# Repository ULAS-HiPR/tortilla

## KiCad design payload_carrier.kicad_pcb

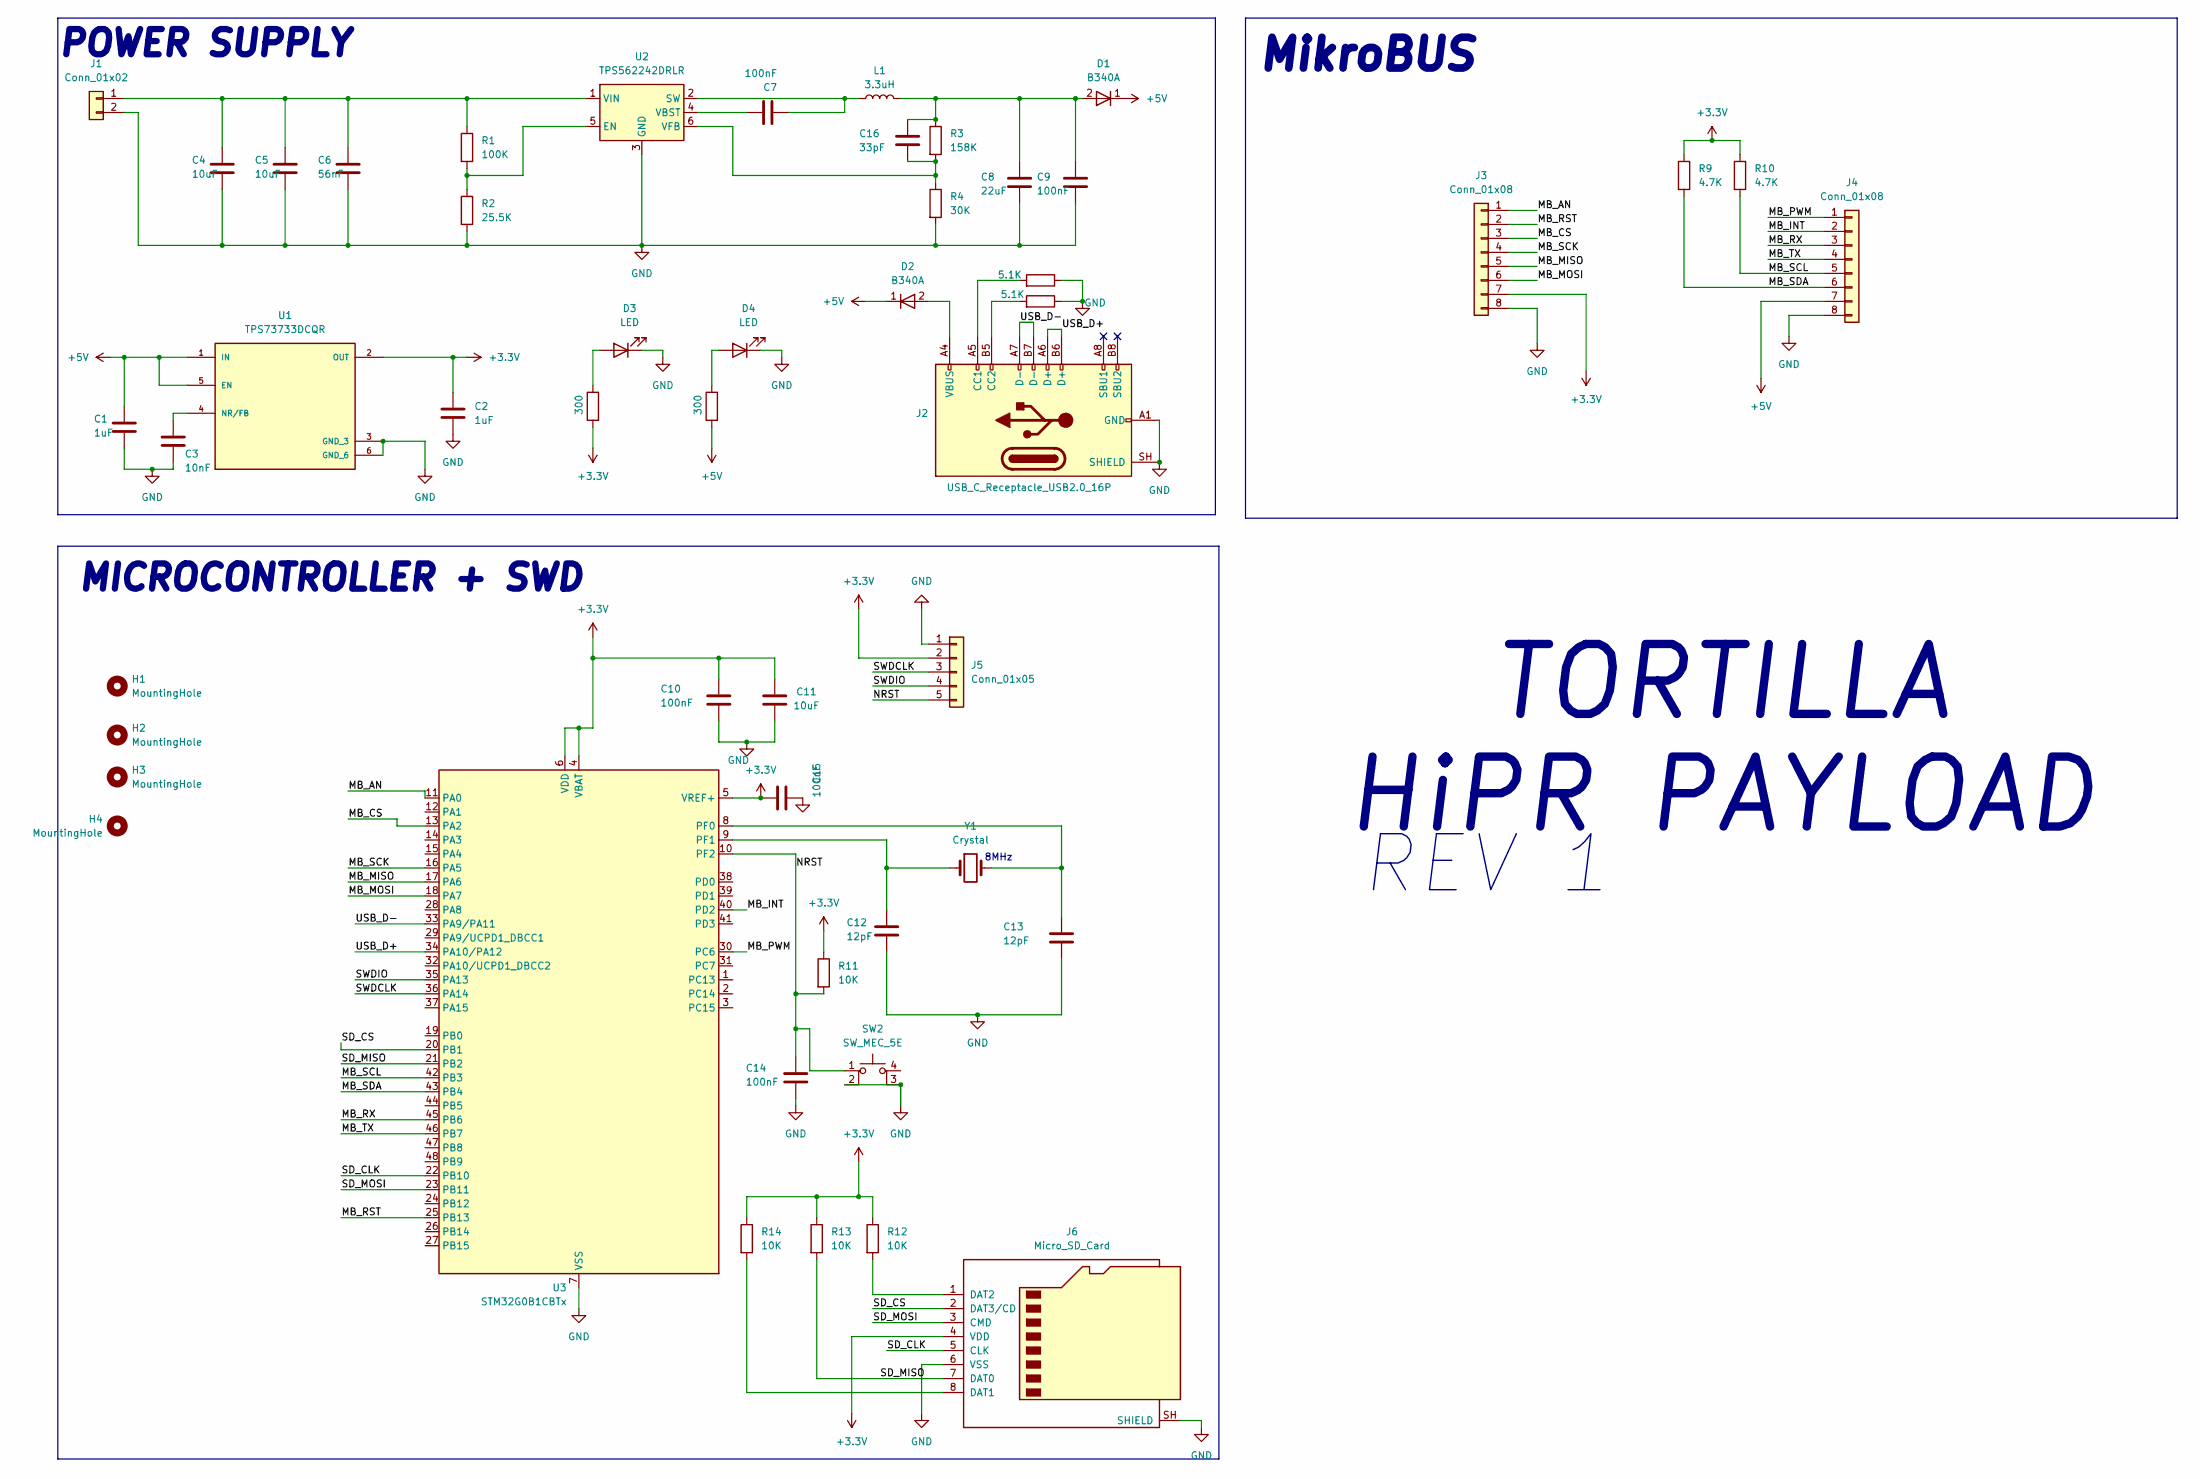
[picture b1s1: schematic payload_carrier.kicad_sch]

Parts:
C1, C2: 1uF; C_0603_1608Metric
C3: 10nF; C_0603_1608Metric
C4, C5, C11: 10uF; C_0805_2012Metric
C6: 56nF; C_0603_1608Metric
C7, C9, C10, C14, C15: 100nF; C_0603_1608Metric
C8: 22uF; C_0805_2012Metric
C12, C13: 12pF; C_0603_1608Metric
C16: 33pF; C_0603_1608Metric
D1, D2: B340A; D_SMA
D3, D4: LED; LED_0603_1608Metric
H1, H2, H3, H4: MountingHole; Mounting_Wuerth_WA-SMSI-M3_H0.5mm_9774005360
J1: Conn_01x02; JST_PH_B2B-PH-K_1x02_P2.00mm_Vertical
J2: USB_C_Receptacle_USB2.0_16P; USB_C_Receptacle_HRO_TYPE-C-31-M-12
J3, J4: Conn_01x08; PinSocket_1x08_P2.54mm_Vertical
J5: Conn_01x05; PinHeader_1x05_P2.54mm_Vertical
J6: Micro_SD_Card; microSD_HC_Wuerth_693072010801
L1: 3.3uH; L_Wuerth_MAPI-4020
R1: 100K; R_0603_1608Metric
R2: 25.5K; R_0603_1608Metric
R3: 158K; R_0603_1608Metric
R4: 30K; R_0603_1608Metric
R5, R6: 5.1K; R_0603_1608Metric
R7, R8: 300; R_0603_1608Metric
R9, R10: 4.7K; R_0603_1608Metric
R11, R12, R13, R14: 10K; R_0603_1608Metric
SW2: SW_MEC_5E; SW_SPST_B3SL-1002P
U1: TPS73733DCQR; IC_TPS73733DCQR; PARTREV R
U2: TPS562242DRLR; SOT-563
U3: STM32G0B1CBTx; LQFP-48_7x7mm_P0.5mm
Y1: Crystal; Crystal_SMD_5032-2Pin_5.0x3.2mm

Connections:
+3.3V: C2.1, C10.1, C11.1, C15.1, J3.7, J5.2, J6.4 (VDD), R7.2, R9.1, R10.1, R11.1, R12.1, R13.1, R14.1, U1.2 (OUT), U3.4 (VBAT), U3.5 (VREF+), U3.6 (VDD)
+5V: C1.1, D1.1 (K), D2.1 (K), J4.7, R8.2, U1.1 (IN), U1.5 (EN)
/MB_AN: J3.1, U3.11 (PA0)
/MB_CS: J3.3, U3.13 (PA2)
/MB_INT: J4.2, U3.40 (PD2)
/MB_MISO: J3.5, U3.17 (PA6)
/MB_MOSI: J3.6, U3.18 (PA7)
/MB_PWM: J4.1, U3.30 (PC6)
/MB_RST: J3.2, U3.25 (PB13)
/MB_RX: J4.3, U3.45 (PB6)
/MB_SCK: J3.4, U3.16 (PA5)
/MB_SCL: J4.5, R10.2, U3.42 (PB3)
/MB_SDA: J4.6, R9.2, U3.43 (PB4)
/MB_TX: J4.4, U3.46 (PB7)
/NRST: C14.1, J5.5, R11.2, SW2.1, U3.10 (PF2)
/SD_CLK: J6.5 (CLK), U3.22 (PB10)
/SD_CS: J6.2 (DAT3/CD), U3.20 (PB1)
/SD_MISO: J6.7 (DAT0), R13.2, U3.21 (PB2)
/SD_MOSI: J6.3 (CMD), U3.23 (PB11)
/SWDCLK: J5.3, U3.36 (PA14)
/SWDIO: J5.4, U3.35 (PA13)
/USB_D+: J2.A6 (D+), J2.B6 (D+), U3.34 (PA10/PA12)
/USB_D-: J2.A7 (D-), J2.B7 (D-), U3.33 (PA9/PA11)
GND: C1.2, C2.2, C3.2, C4.2, C5.2, C6.2, C8.2, C9.2, C10.2, C11.2, C12.2, C13.2, C14.2, C15.2, D3.1 (K), D4.1 (K), J1.2, J2.A1 (GND), J2.A12 (GND), J2.B1 (GND), J2.B12 (GND), J2.SH (SHIELD), J3.8, J4.8, J5.1, J6.6 (VSS), J6.SH (SHIELD), R2.2, R4.2, R5.1, R6.1, SW2.2, SW2.3 (K), U1.3 (GND_3), U1.6 (GND_6), U2.3 (GND), U3.7 (VSS)
unnamed: C8.1, C9.1, C16.1, D1.2 (A), L1.2, R3.1
unnamed: D2.2 (A), J2.A4 (VBUS), J2.A9 (VBUS), J2.B4 (VBUS), J2.B9 (VBUS)
unnamed: D3.2 (A), R7.1
unnamed: D4.2 (A), R8.1
unnamed: C4.1, C5.1, C6.1, J1.1, R1.1, U2.1 (VIN)
unnamed: J2.A5 (CC1), R6.2
unnamed: J2.B5 (CC2), R5.2
unnamed: J6.8 (DAT1), R14.2
unnamed: J6.1 (DAT2), R12.2
unnamed: C3.1, U1.4 (NR/FB)
unnamed: R1.2, R2.1, U2.5 (EN)
unnamed: C7.2, L1.1, U2.2 (SW)
unnamed: C7.1, U2.4 (VBST)
unnamed: C16.2, R3.2, R4.1, U2.6 (VFB)
unnamed: C13.1, U3.8 (PF0), Y1.2
unnamed: C12.1, U3.9 (PF1), Y1.1

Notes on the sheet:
MikroBUS
TORTILLA HiPR PAYLOAD
REV 1
MICROCONTROLLER + SWD
8MHz
POWER SUPPLY

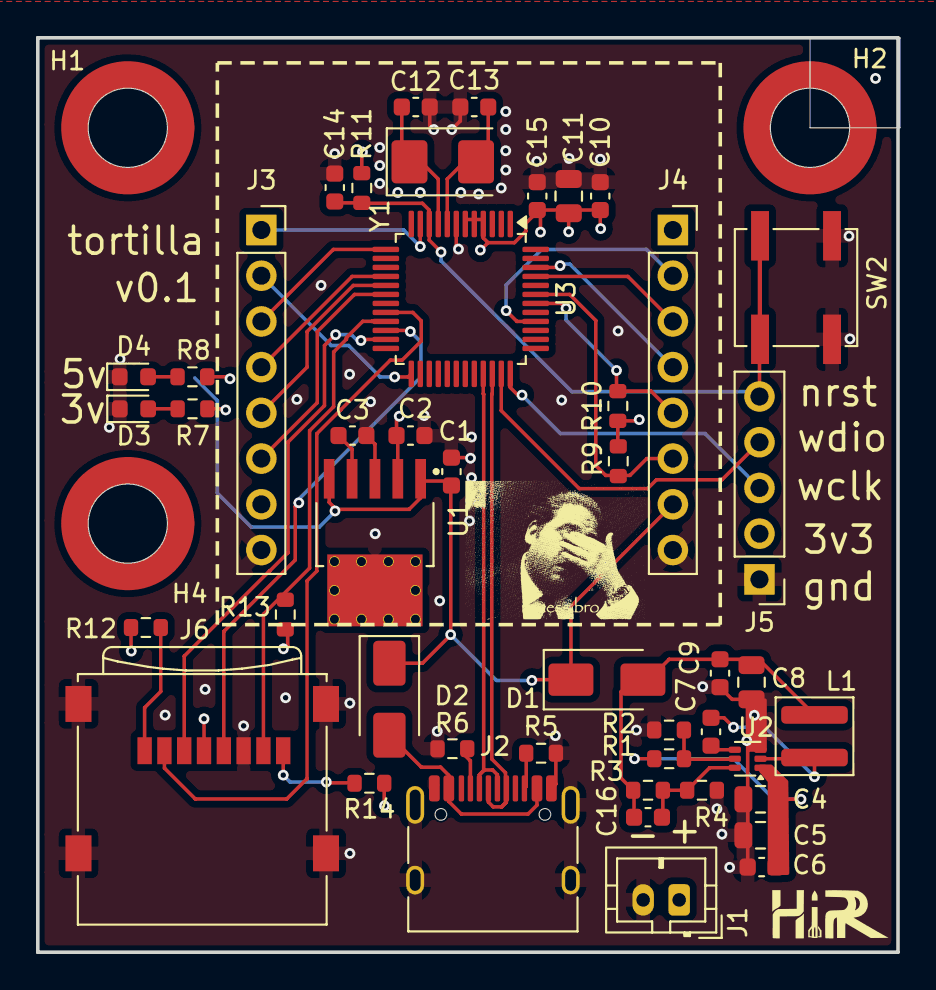
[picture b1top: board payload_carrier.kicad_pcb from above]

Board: 4 copper layers, 47.8 x 50.8 mm, 49 parts (0 on the bottom side), 40 nets.
